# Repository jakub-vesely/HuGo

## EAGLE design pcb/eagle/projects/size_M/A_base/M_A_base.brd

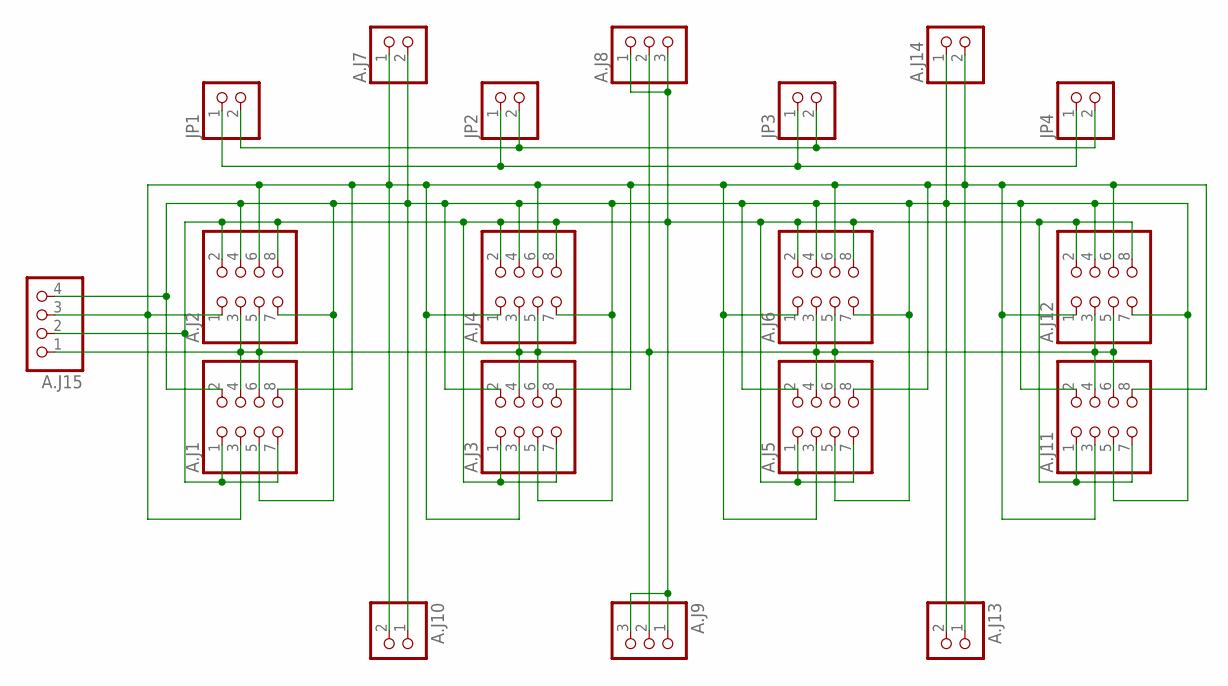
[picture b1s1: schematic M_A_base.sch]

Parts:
A.J1, A.J2, A.J3, A.J4, A.J5, A.J6, A.J11, A.J12: PINHD-2X4; 2X04
A.J7, A.J14: PINHD-1X2/90; 1X02/90
A.J8: PINHD-1X3/90; 1X03/90
A.J9: PINHD-1X31X03/90F; 1X03/90F
A.J10, A.J13: PINHD-1X21X02/90F; 1X02/90F
A.J15: PINHD-1X4; 1X04
JP1, JP2, JP3, JP4: PINHD-1X2; 1X02

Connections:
GND: A.J1.1, A.J1.7, A.J2.2, A.J2.8, A.J3.1, A.J3.7, A.J4.2, A.J4.8, A.J5.1, A.J5.7, A.J6.2, A.J6.8, A.J8.1, A.J8.3, A.J9.1, A.J9.3, A.J11.1, A.J11.7, A.J12.2, A.J12.8, A.J15.2
SCL: A.J1.2, A.J1.5, A.J2.4, A.J2.7, A.J3.2, A.J3.5, A.J4.4, A.J4.7, A.J5.2, A.J5.5, A.J6.4, A.J6.7, A.J7.2, A.J10.1, A.J11.2, A.J11.5, A.J12.4, A.J12.7, A.J13.2, A.J14.1, A.J15.4
SDA: A.J1.3, A.J1.8, A.J2.1, A.J2.6, A.J3.3, A.J3.8, A.J4.1, A.J4.6, A.J5.3, A.J5.8, A.J6.1, A.J6.6, A.J7.1, A.J10.2, A.J11.3, A.J11.8, A.J12.1, A.J12.6, A.J13.1, A.J14.2, A.J15.3
VBAT: JP1.2, JP2.2, JP3.2, JP4.2
VCC: A.J1.4, A.J1.6, A.J2.3, A.J2.5, A.J3.4, A.J3.6, A.J4.3, A.J4.5, A.J5.4, A.J5.6, A.J6.3, A.J6.5, A.J8.2, A.J9.2, A.J11.4, A.J11.6, A.J12.3, A.J12.5, A.J15.1
VUSB: JP1.1, JP2.1, JP3.1, JP4.1

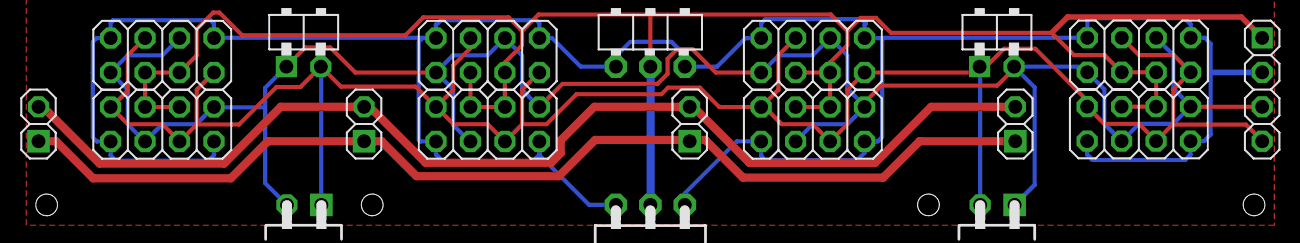
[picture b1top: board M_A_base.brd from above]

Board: 2 copper layers, 19 parts (0 on the bottom side), 6 nets.

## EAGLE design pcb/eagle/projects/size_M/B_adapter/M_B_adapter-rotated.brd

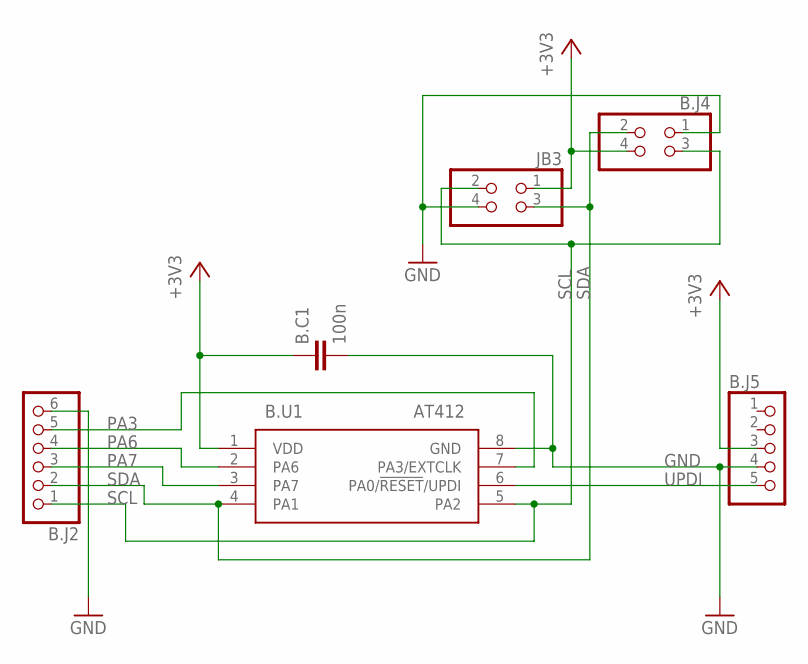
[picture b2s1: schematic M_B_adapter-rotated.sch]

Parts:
B.C1: 100n; C0603
B.J2: PINHD-1X6; 1X06
B.J4: PINHD-2X2; 2X02
B.J5: PINHD-1X5; 1X05
B.U1: AT412; SOIC127P600X175-8N
JB3: PINHD-2X2; 2X02

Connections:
3V3: B.C1.1, B.J4.4, B.J5.3, B.U1.1 (VDD), JB3.1
GND: B.C1.2, B.J2.6, B.J4.1, B.J5.4, B.U1.8 (GND), JB3.4
PA3: B.J2.5, B.U1.7 (PA3/EXTCLK)
PA6: B.J2.4, B.U1.2 (PA6)
PA7: B.J2.3, B.U1.3 (PA7)
SCL: B.J2.1, B.J4.3, B.U1.5 (PA2), JB3.2
SDA: B.J2.2, B.J4.2, B.U1.4 (PA1), JB3.3
UPDI: B.J5.5, B.U1.6 (PA0/!RESET!/UPDI)

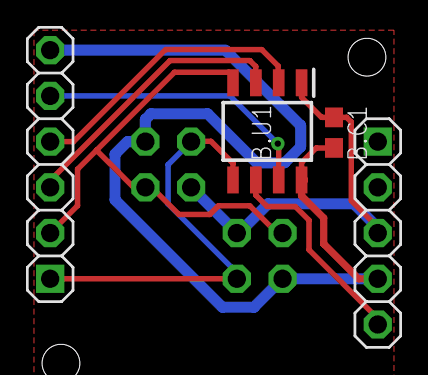
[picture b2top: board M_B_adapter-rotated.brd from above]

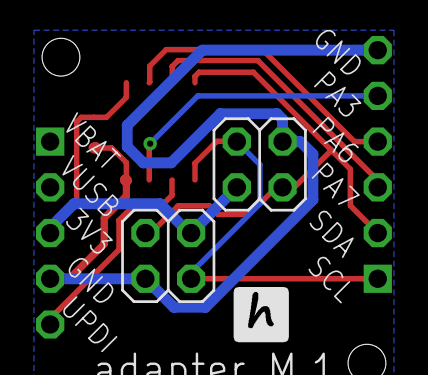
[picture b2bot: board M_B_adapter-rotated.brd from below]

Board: 2 copper layers, 6 parts (2 on the bottom side), 8 nets.

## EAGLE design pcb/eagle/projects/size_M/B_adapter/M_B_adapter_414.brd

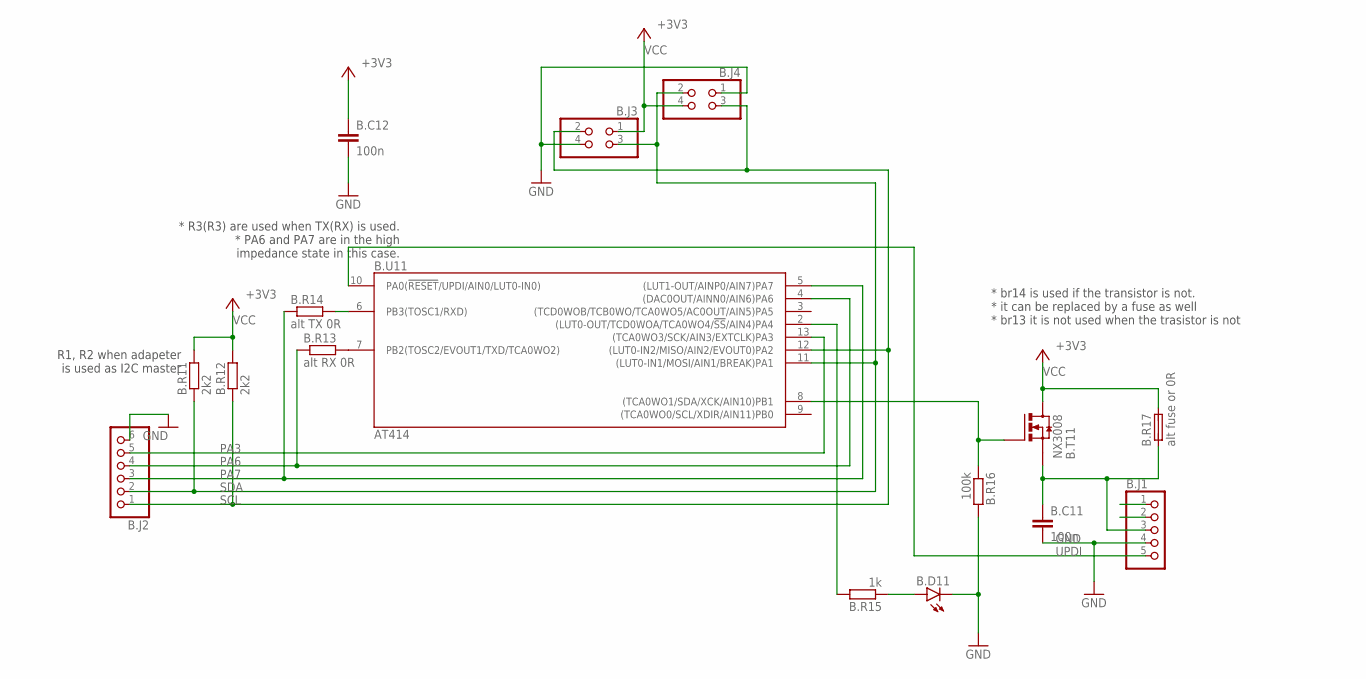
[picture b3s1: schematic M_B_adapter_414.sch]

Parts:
B.C11, B.C12: 100n; C0603
B.D11: LEDCHIP-LED0603; CHIP-LED0603
B.J1: PINHD-1X5; 1X05
B.J2: PINHD-1X6; 1X06
B.J3, B.J4: PINHD-2X2; 2X02
B.R11, B.R12: 2k2; R0603
B.R13: alt RX 0R; R0603
B.R14: alt TX 0R; R0603
B.R15: 1k; R0603
B.R16: 100k; R0603
B.R17: alt fuse or 0R; FUSE
B.T11: NX3008; SO23
B.U11: AT414; SO14

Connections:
GND: B.C11.2, B.C12.2, B.D11.C1 (C), B.J1.4, B.J2.6, B.J3.4, B.J4.1, B.R16.2, B.U11.14 (GND)
unnamed: B.R14.2, B.U11.6 (PB3(TOSC1/RXD))
unnamed: B.R13.2, B.U11.7 (PB2(TOSC2/EVOUT1/TXD/TCA0WO2))
unnamed: B.R16.1, B.T11.G, B.U11.8 ((TCA0WO1/SDA/XCK/AIN10)PB1)
unnamed: B.C11.1, B.J1.3, B.R17.1, B.T11.S
unnamed: B.R15.2, B.U11.2 ((LUT0-OUT/TCD0WOA/TCA0WO4/!SS!/AIN4)PA4)
PA1: B.D11.A1 (A), B.R15.1
PA3: B.J2.5, B.U11.13 ((TCA0WO3/SCK/AIN3/EXTCLK)PA3)
PA6: B.J2.4, B.R13.1, B.U11.4 ((DAC0OUT/AINN0/AIN6)PA6)
PA7: B.J2.3, B.R14.1, B.U11.5 ((LUT1-OUT/AINP0/AIN7)PA7)
SCL: B.J2.1, B.J3.2, B.J4.3, B.R12.1, B.U11.12 ((LUT0-IN2/MISO/AIN2/EVOUT0)PA2)
SDA: B.J2.2, B.J3.3, B.J4.2, B.R11.1, B.U11.11 ((LUT0-IN1/MOSI/AIN1/BREAK)PA1)
UPDI: B.J1.5, B.U11.10 (PA0(!RESET!/UPDI/AIN0/LUT0-IN0))
VBAT: B.J1.2
VCC: B.C12.1, B.J3.1, B.J4.4, B.R11.2, B.R12.2, B.R17.2, B.T11.D, B.U11.1 (VCC)
VUSB: B.J1.1

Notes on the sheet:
* br14 is used if the transistor is not. * it can be replaced by a fuse as well * br13 it is not used when the trasistor is not
* R3(R3) are used when TX(RX) is used. * PA6 and PA7 are in the high impedance state in this case.
R1, R2 when adapeter is used as I2C master

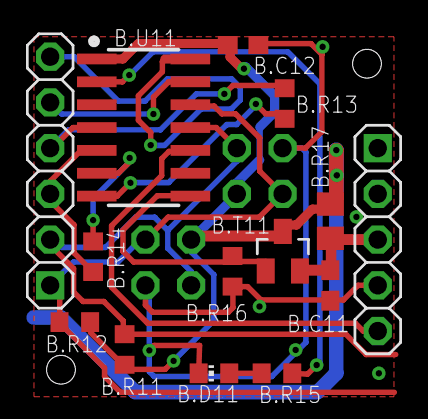
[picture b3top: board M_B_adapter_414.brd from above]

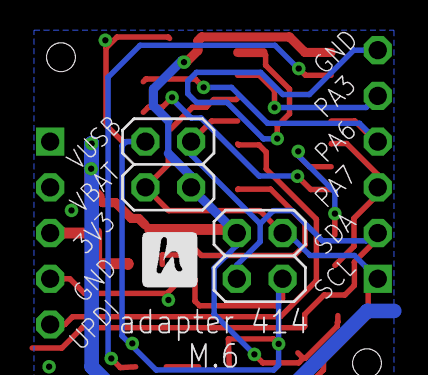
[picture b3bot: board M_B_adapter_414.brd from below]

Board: 2 copper layers, 16 parts (2 on the bottom side), 14 nets.

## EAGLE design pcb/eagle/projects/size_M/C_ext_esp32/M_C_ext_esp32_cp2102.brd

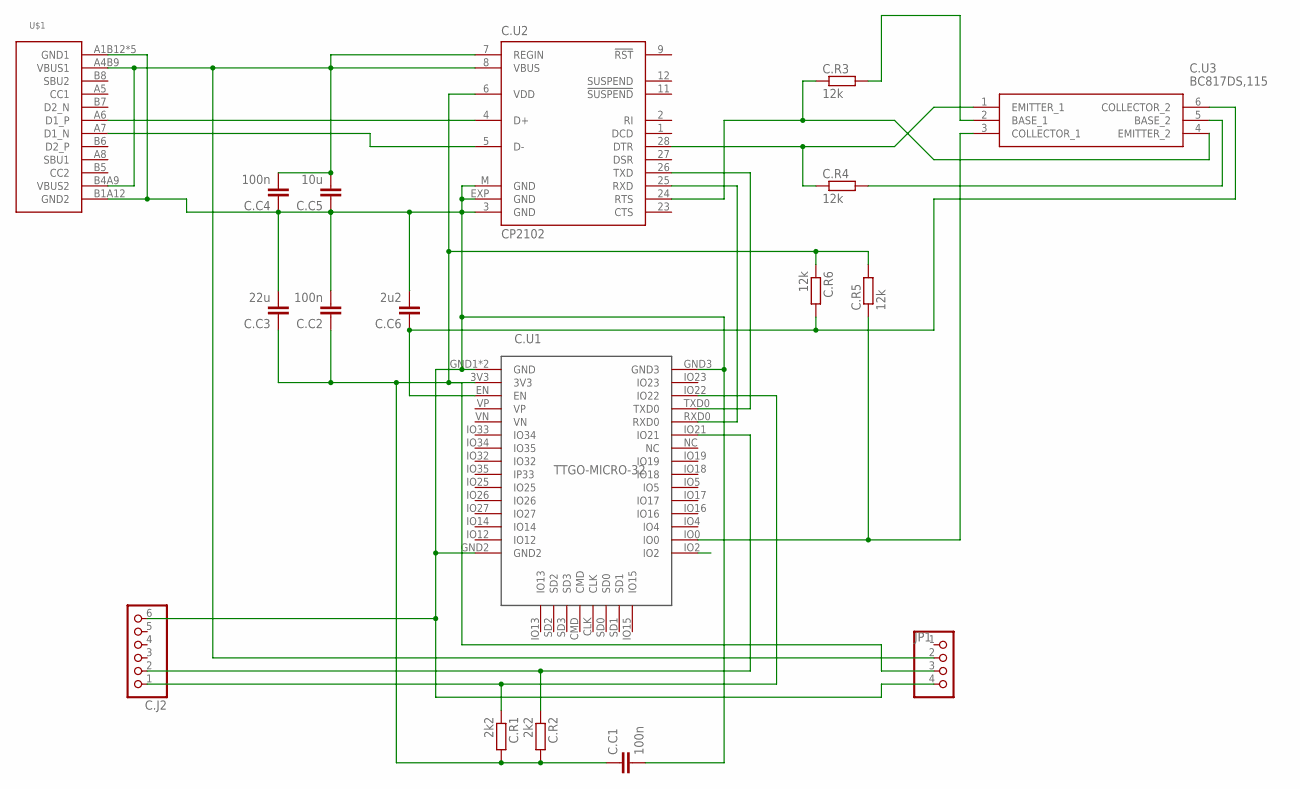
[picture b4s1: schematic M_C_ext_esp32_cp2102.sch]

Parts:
C.C1, C.C2, C.C4: 100n; C0603
C.C3: 22u; C0805
C.C5: 10u; C0603
C.C6: 2u2; C0603
C.J2: PINHD-1X6; 1X06
C.R1, C.R2: 2k2; R0603
C.R3, C.R4, C.R5, C.R6: 12k; R0603
C.U1: TTGO-MICRO-32
C.U2: CP2102; MLP28
C.U3: BC817DS,115; SOT95P275X110-6N
JP1: PINHD-1X4; 1X04
U$1: USB-C

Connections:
GND: C.C1.2, C.C2.2, C.C3.2, C.C4.1, C.C5.1, C.C6.2, C.J2.6, C.U1.GND1 (GND), C.U1.GND2, C.U1.GND3, C.U1.GND4 (GND), C.U2.3 (GND), C.U2.EXP (GND), C.U2.M (GND), JP1.4, U$1.A1B12 (GND1), U$1.B1A12 (GND2), U$1.SH1 (GND1), U$1.SH2 (GND1), U$1.SH3 (GND1), U$1.SH4 (GND1)
unnamed: C.U2.5 (D-), U$1.A7 (D1_N)
unnamed: C.U2.4 (D+), U$1.A6 (D1_P)
unnamed: C.R4.2, C.U3.5 (BASE_2)
unnamed: C.R3.2, C.U3.2 (BASE_1)
unnamed: C.R3.1, C.U2.24 (RTS), C.U3.4 (EMITTER_2)
unnamed: C.R4.1, C.U2.28 (DTR), C.U3.1 (EMITTER_1)
unnamed: C.R5.1, C.U1.IO0, C.U3.3 (COLLECTOR_1)
unnamed: C.C6.1, C.R6.2, C.U1.EN, C.U3.6 (COLLECTOR_2)
RX: C.U1.RXD0, C.U2.25 (RXD)
SCL: C.J2.1, C.R1.1, C.U1.IO22
SDA: C.J2.2, C.R2.1, C.U1.IO21
TX: C.U1.TXD0, C.U2.26 (TXD)
VDD: C.C1.1, C.C2.1, C.C3.1, C.R1.2, C.R2.2, C.R5.2, C.R6.1, C.U1.3V3, C.U2.6 (VDD), JP1.3
VUSB: C.C4.2, C.C5.2, C.U2.7 (REGIN), C.U2.8 (VBUS), JP1.2, U$1.A4B9 (VBUS1), U$1.B4A9 (VBUS2)

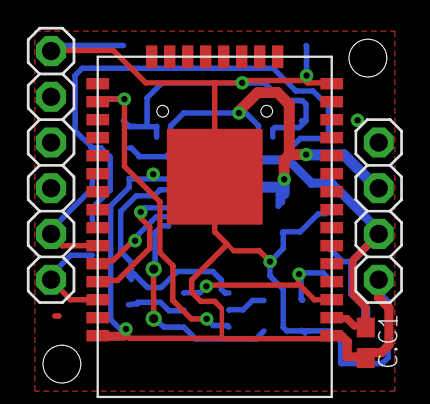
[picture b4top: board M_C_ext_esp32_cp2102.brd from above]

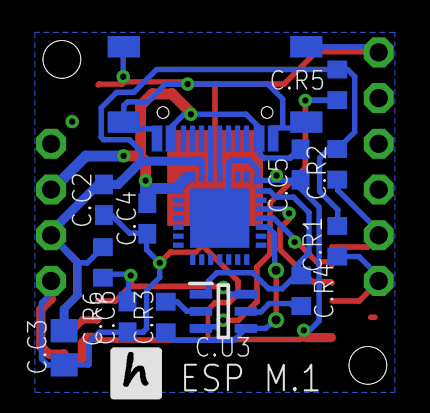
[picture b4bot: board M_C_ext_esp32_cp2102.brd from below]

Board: 2 copper layers, 18 parts (14 on the bottom side), 15 nets.

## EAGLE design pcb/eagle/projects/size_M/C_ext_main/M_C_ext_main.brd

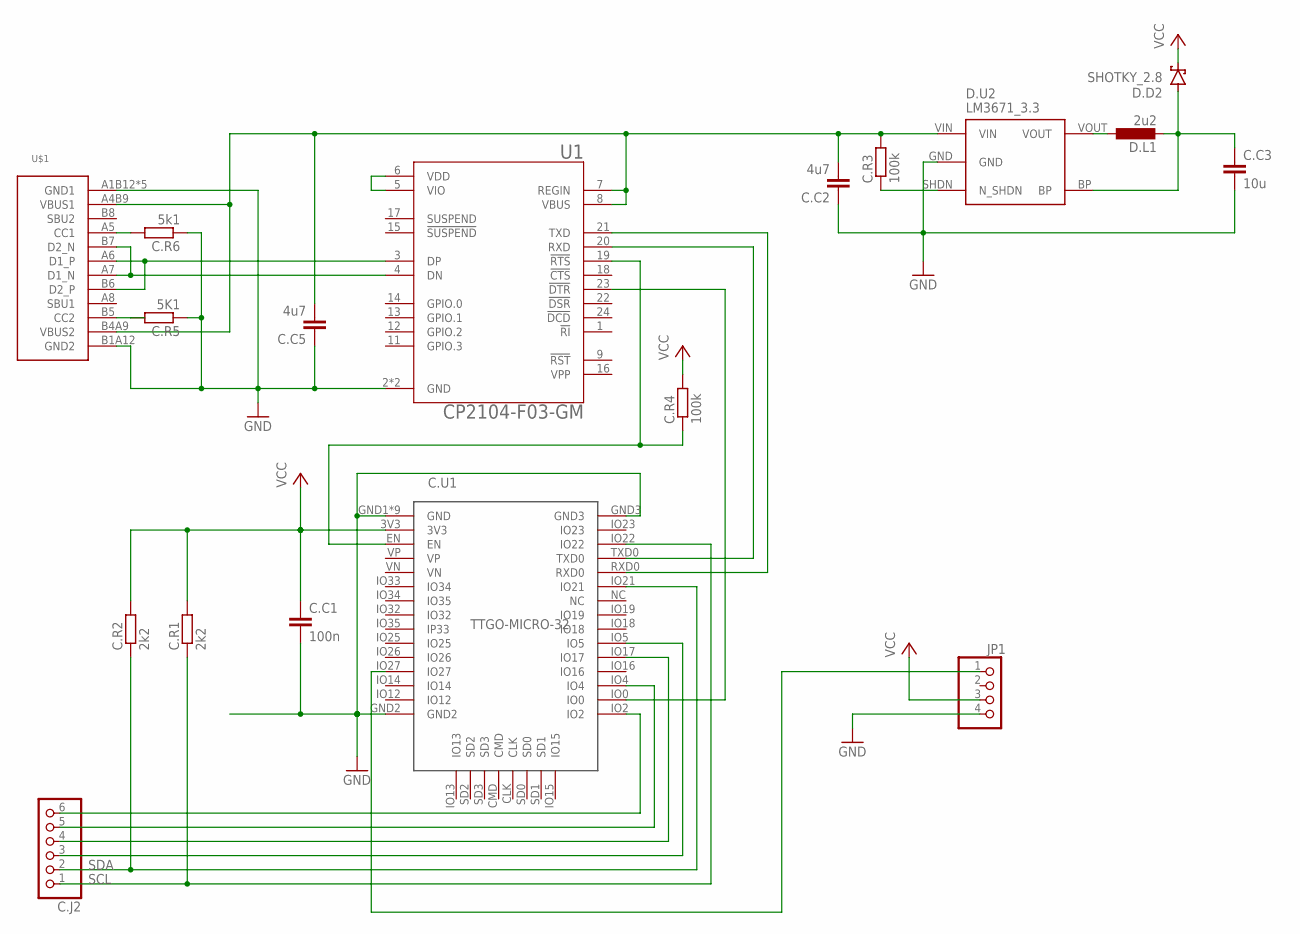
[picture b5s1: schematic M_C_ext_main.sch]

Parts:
C.C1: 100n; C0603
C.C2, C.C5: 4u7; C0603
C.C3: 10u; C0805
C.J2: PINHD-1X6; 1X06
C.R1, C.R2: 2k2; R0603
C.R3, C.R4: 100k; R0603
C.R5: 5K1; R0603
C.R6: 5k1; R0603
C.U1: TTGO-MICRO-32
D.D2: SHOTKY_2.8
D.L1: 2u2; L3230M
D.U2: LM3671_3.3; SOT32-5
JP1: PINHD-1X4; 1X04
U1: CP2104-F03-GM; QFN50P400X400X80-25N
U$1: USB-C

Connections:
GND: C.C1.2, C.C2.1, C.C3.2, C.C5.1, C.R5.1, C.R6.1, C.U1.GND1 (GND), C.U1.GND2, C.U1.GND3, C.U1.GND4 (GND), C.U1.GND5 (GND), C.U1.GND6 (GND), C.U1.GND7 (GND), C.U1.GND8 (GND), C.U1.GND9 (GND), C.U1.GND10 (GND), C.U1.GND11 (GND), D.U2.GND, JP1.4, U1.2 (GND), U1.25 (GND), U$1.A1B12 (GND1), U$1.B1A12 (GND2), U$1.SH1 (GND1), U$1.SH2 (GND1), U$1.SH3 (GND1), U$1.SH4 (GND1)
unnamed: U1.4 (DN), U$1.A7 (D1_N), U$1.B7 (D2_N)
unnamed: U1.3 (DP), U$1.A6 (D1_P), U$1.B6 (D2_P)
unnamed: C.R6.2, U$1.A5 (CC1)
unnamed: C.R5.2, U$1.B5 (CC2)
unnamed: C.C3.1, D.D2.A, D.L1.2, D.U2.BP
unnamed: C.J2.6, C.U1.IO2
unnamed: U1.5 (VIO), U1.6 (VDD)
unnamed: D.L1.1, D.U2.VOUT
unnamed: C.R3.1, D.U2.SHDN (N_SHDN)
unnamed: C.J2.5, C.U1.IO4
unnamed: C.J2.4, C.U1.IO17
unnamed: C.J2.3, C.U1.IO5
unnamed: C.U1.IO27, JP1.1
PROG: C.U1.IO0, U1.23 (!DTR)
RESET: C.R4.1, C.U1.EN, U1.19 (!RTS)
RX: C.U1.TXD0, U1.20 (RXD)
SCL: C.J2.1, C.R1.1, C.U1.IO22
SDA: C.J2.2, C.R2.1, C.U1.IO21
TX: C.U1.RXD0, U1.21 (TXD)
VCC: C.C1.1, C.R1.2, C.R2.2, C.R4.2, C.U1.3V3, D.D2.K (C), JP1.3
VUSB: C.C2.2, C.C5.2, C.R3.2, D.U2.VIN, U1.7 (REGIN), U1.8 (VBUS), U$1.A4B9 (VBUS1), U$1.B4A9 (VBUS2)

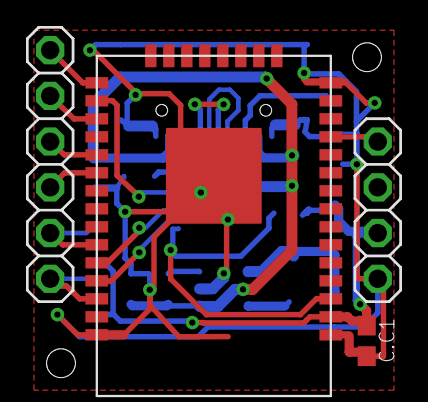
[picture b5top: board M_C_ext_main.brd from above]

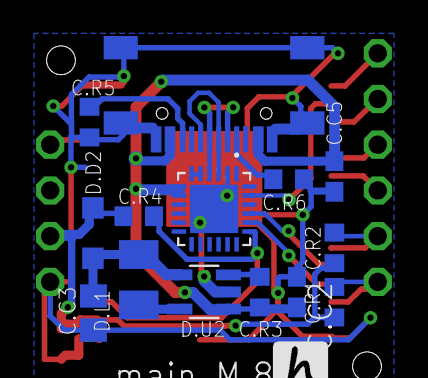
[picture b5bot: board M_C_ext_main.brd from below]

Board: 2 copper layers, 18 parts (14 on the bottom side), 22 nets.
